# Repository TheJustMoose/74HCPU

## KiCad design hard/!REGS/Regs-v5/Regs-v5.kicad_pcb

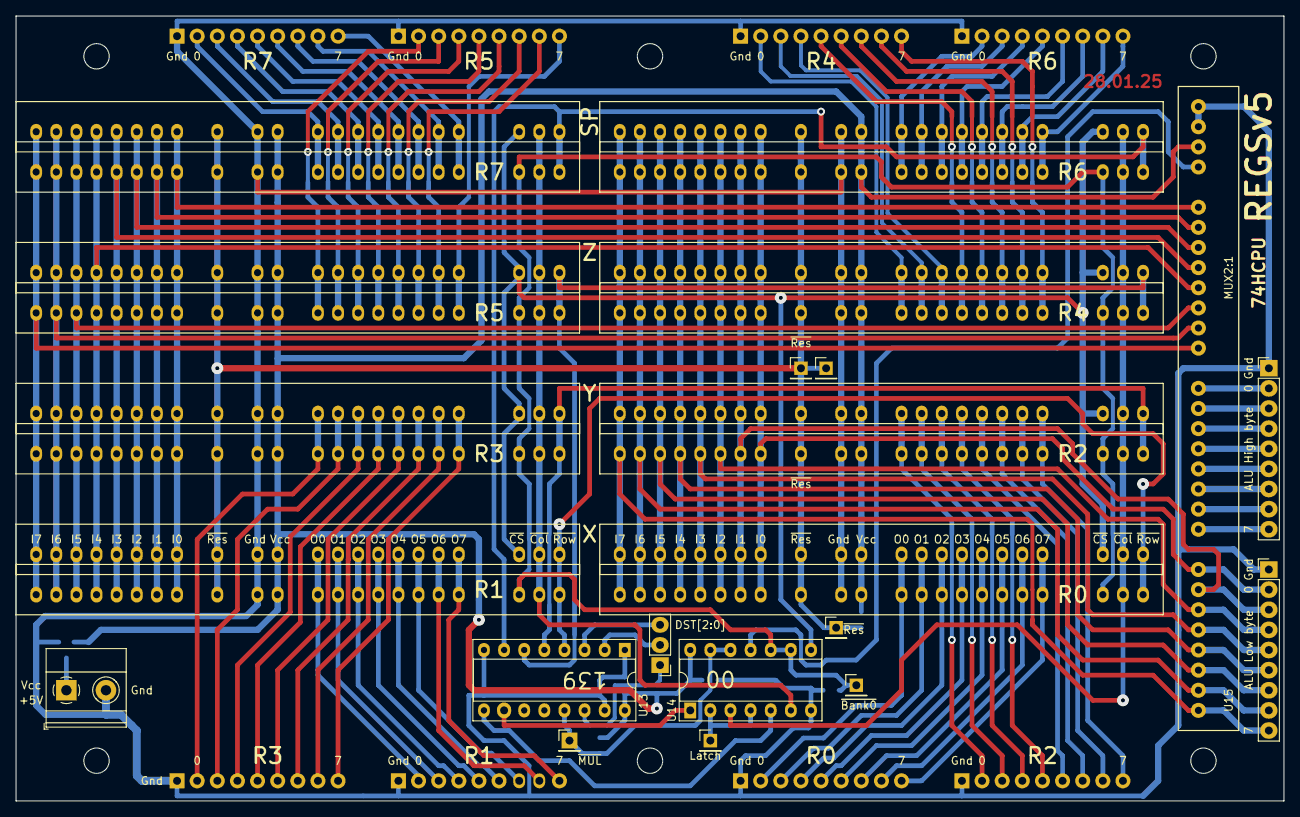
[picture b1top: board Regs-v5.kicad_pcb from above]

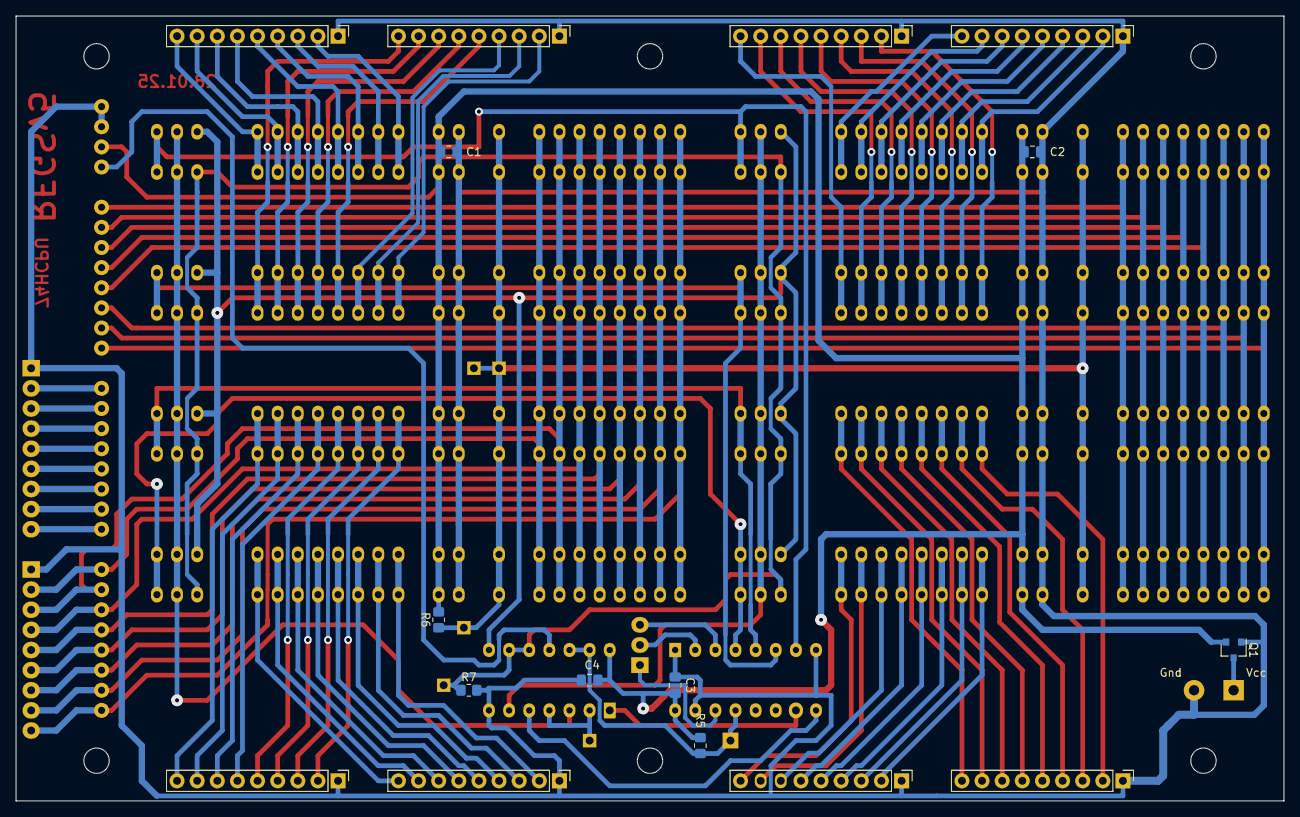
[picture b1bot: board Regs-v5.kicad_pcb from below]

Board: 2 copper layers, 160.0 x 99.1 mm, 51 parts (16 on the bottom side), 108 nets.

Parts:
C1, C2, C3, C4: 0.1uF; C_0805_2012Metric_Pad1.18x1.45mm_HandSolder
H1, H2, H3, H4, H5, H6: MountingHole; MountingHole_3.2mm_M3
J1, J2, J3, J4, J5, J6, J7, J8, J17, J18: Conn_01x09_Male; PinHeader_1x09_P2.54mm_Vertical
J11: Conn_01x03_Male; PinHeader_1x03_P2.54mm_Vertical
J12, J13, J14, J15, J19, J20: Conn_01x01_Male; PinHeader_1x01_P2.54mm_Vertical
J16: Screw_Terminal_01x02; TerminalBlock_Phoenix_MKDS-1,5-2_1x02_P5.00mm_Horizontal
Q1: IRLML5203; SOT-23
R5, R6, R7: 10k; R_0805_2012Metric_Pad1.20x1.40mm_HandSolder
U1, U2, U3, U4, U5, U6, U7, U8, U9, U10, U11, U12, U16, U17, U18, U19: REG_CNT
U13: 74LS139; DIP-16_W7.62mm_Socket
U14: 74HC00; DIP-14_W7.62mm_Socket
U15: MUX2-1; CMDwoC

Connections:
/ALU_H0: J18.2, U15.16
/ALU_H7: J18.9, U15.9
/DST[0]: J11.1, U13.14
/DST[1]: J11.2, U13.2
/DST[2]: J11.3, U13.3
/H0: U2.8, U4.8, U6.8, U8.8, U10.8, U12.8, U15.24, U17.8, U19.8
/H1: U2.7, U4.7, U6.7, U8.7, U10.7, U12.7, U15.23, U17.7, U19.7
/H2: U2.6, U4.6, U6.6, U8.6, U10.6, U12.6, U15.22, U17.6, U19.6
/H3: U2.5, U4.5, U6.5, U8.5, U10.5, U12.5, U15.21, U17.5, U19.5
/H4: U2.4, U4.4, U6.4, U8.4, U10.4, U12.4, U15.20, U17.4, U19.4
/H5: U2.3, U4.3, U6.3, U8.3, U10.3, U12.3, U15.19, U17.3, U19.3
/H6: U2.2, U4.2, U6.2, U8.2, U10.2, U12.2, U15.18, U17.2, U19.2
/H7: U2.1, U4.1, U6.1, U8.1, U10.1, U12.1, U15.17, U17.1, U19.1
/L0: J17.2, U1.8, U3.8, U5.8, U7.8, U9.8, U11.8, U15.8, U16.8, U18.8
/L1: J17.3, U1.7, U3.7, U5.7, U7.7, U9.7, U11.7, U15.7, U16.7, U18.7
/L2: J17.4, U1.6, U3.6, U5.6, U7.6, U9.6, U11.6, U15.6, U16.6, U18.6
/L3: J17.5, U1.5, U3.5, U5.5, U7.5, U9.5, U11.5, U15.5, U16.5, U18.5
/L4: J17.6, U1.4, U3.4, U5.4, U7.4, U9.4, U11.4, U15.4, U16.4, U18.4
/L5: J17.7, U1.3, U3.3, U5.3, U7.3, U9.3, U11.3, U15.3, U16.3, U18.3
/L6: J17.8, U1.2, U3.2, U5.2, U7.2, U9.2, U11.2, U15.2, U16.2, U18.2
/L7: J17.9, U1.1, U3.1, U5.1, U7.1, U9.1, U11.1, U15.1, U16.1, U18.1
/Latch: J15.1, U14.2, U14.4
/R0.0: J1.2, U1.12, U9.12
/R0.1: J1.3, U1.13, U9.13
/R0.2: J1.4, U1.14, U9.14
/R0.3: J1.5, U1.15, U9.15
/R0.4: J1.6, U1.16, U9.16
/R0.5: J1.7, U1.17, U9.17
/R0.6: J1.8, U1.18, U9.18
/R0.7: J1.9, U1.19, U9.19
/R1.0: J2.2, U2.12, U10.12
/R1.1: J2.3, U2.13, U10.13
/R1.2: J2.4, U2.14, U10.14
/R1.3: J2.5, U2.15, U10.15
/R1.4: J2.6, U2.16, U10.16
/R1.5: J2.7, U2.17, U10.17
/R1.6: J2.8, U2.18, U10.18
/R1.7: J2.9, U2.19, U10.19
/R2.0: J3.2, U3.12, U11.12
/R2.1: J3.3, U3.13, U11.13
/R2.2: J3.4, U3.14, U11.14
/R2.3: J3.5, U3.15, U11.15
/R2.4: J3.6, U3.16, U11.16
/R2.5: J3.7, U3.17, U11.17
/R2.6: J3.8, U3.18, U11.18
/R2.7: J3.9, U3.19, U11.19
/R3.0: J4.2, U4.12, U12.12
/R3.1: J4.3, U4.13, U12.13
/R3.2: J4.4, U4.14, U12.14
/R3.3: J4.5, U4.15, U12.15
/R3.4: J4.6, U4.16, U12.16
/R3.5: J4.7, U4.17, U12.17
/R3.6: J4.8, U4.18, U12.18
/R3.7: J4.9, U4.19, U12.19
/R4.0: J5.2, U5.12, U16.12
/R4.1: J5.3, U5.13, U16.13
/R4.2: J5.4, U5.14, U16.14
/R4.3: J5.5, U5.15, U16.15
/R4.4: J5.6, U5.16, U16.16
/R4.5: J5.7, U5.17, U16.17
/R4.6: J5.8, U5.18, U16.18
/R4.7: J5.9, U5.19, U16.19
/R5.0: J6.2, U6.12, U17.12
/R5.1: J6.3, U6.13, U17.13
/R5.2: J6.4, U6.14, U17.14
/R5.3: J6.5, U6.15, U17.15
/R5.4: J6.6, U6.16, U17.16
/R5.5: J6.7, U6.17, U17.17
/R5.6: J6.8, U6.18, U17.18
/R5.7: J6.9, U6.19, U17.19
/R6.0: J7.2, U7.12, U18.12
/R6.1: J7.3, U7.13, U18.13
/R6.2: J7.4, U7.14, U18.14
/R6.3: J7.5, U7.15, U18.15
/R6.4: J7.6, U7.16, U18.16
/R6.5: J7.7, U7.17, U18.17
/R6.6: J7.8, U7.18, U18.18
/R6.7: J7.9, U7.19, U18.19
/R7.0: J8.2, U8.12, U19.12
/R7.1: J8.3, U8.13, U19.13
/R7.2: J8.4, U8.14, U19.14
/R7.3: J8.5, U8.15, U19.15
/R7.4: J8.6, U8.16, U19.16
/R7.5: J8.7, U8.17, U19.17
/R7.6: J8.8, U8.18, U19.18
/R7.7: J8.9, U8.19, U19.19
/~Bank0: J14.1, R7.1, U1.20, U2.20, U3.20, U4.20, U5.20, U6.20, U7.20, U8.20, U14.9, U14.10
/~Bank1: U9.20, U10.20, U11.20, U12.20, U14.8, U16.20, U17.20, U18.20, U19.20
/~H: U2.21, U4.21, U6.21, U8.21, U10.21, U12.21, U14.6, U17.21, U19.21
/~L: U1.21, U3.21, U5.21, U7.21, U9.21, U11.21, U14.3, U16.21, U18.21
/~MUL: J12.1, R5.1, U13.13, U14.12, U14.13
/~R0: U1.22, U2.22, U9.22, U10.22, U13.4
/~R1: U3.22, U4.22, U11.22, U12.22, U13.5
/~R2: U5.22, U6.22, U13.6, U16.22, U17.22
/~R3: U7.22, U8.22, U13.7, U18.22, U19.22
/~Res: J13.1, J19.1, J20.1, R6.1, U1.9, U2.9, U3.9, U4.9, U5.9, U6.9, U7.9, U8.9, U9.9, U10.9, U11.9, U12.9, U16.9, U17.9, U18.9, U19.9
GND: C1.2, C2.2, C3.2, C4.2, J1.1, J2.1, J3.1, J4.1, J5.1, J6.1, J7.1, J8.1, J16.2, J17.1, J18.1, Q1.1, R7.2, U1.10, U2.10, U3.10, U4.10, U5.10, U6.10, U7.10, U8.10, U9.10, U10.10, U11.10, U12.10, U13.1, U13.8, U13.15, U14.7, U15.27, U15.28, U16.10, U17.10, U18.10, U19.10
unnamed: J16.1, Q1.3
unnamed: J18.3, U15.15
unnamed: J18.4, U15.14
unnamed: J18.5, U15.13
unnamed: J18.6, U15.12
unnamed: J18.7, U15.11
unnamed: J18.8, U15.10
unnamed: U13.9, U14.5
unnamed: U13.10, U14.1
unnamed: U14.11, U15.25
VCC: C1.1, C2.1, C3.1, C4.1, Q1.2, R5.2, R6.2, U1.11, U2.11, U3.11, U4.11, U5.11, U6.11, U7.11, U8.11, U9.11, U10.11, U11.11, U12.11, U13.16, U14.14, U15.26, U16.11, U17.11, U18.11, U19.11

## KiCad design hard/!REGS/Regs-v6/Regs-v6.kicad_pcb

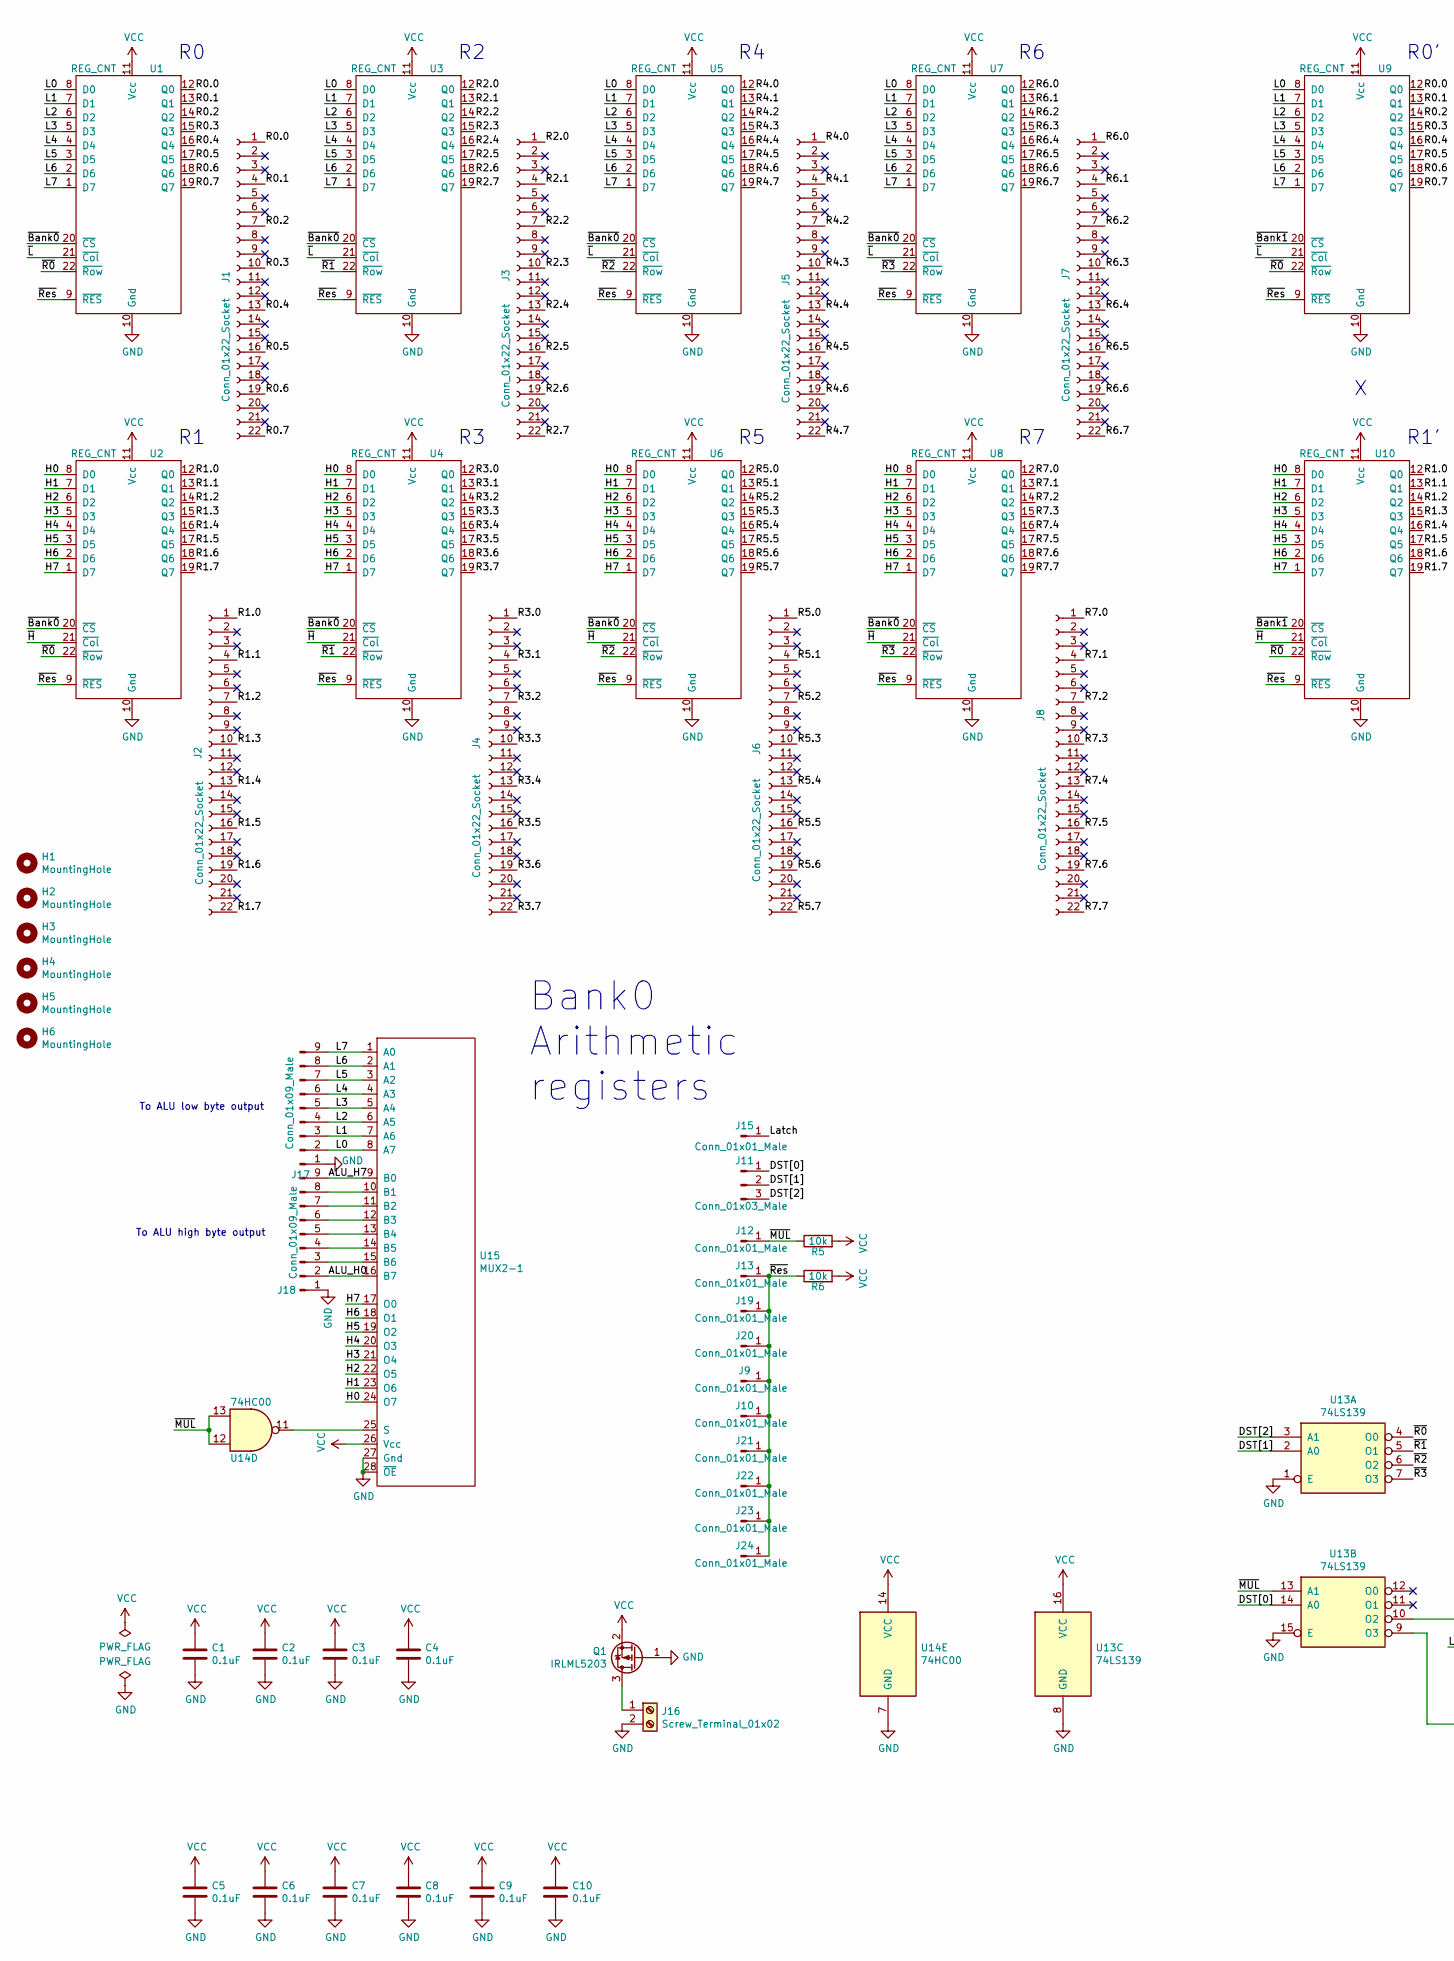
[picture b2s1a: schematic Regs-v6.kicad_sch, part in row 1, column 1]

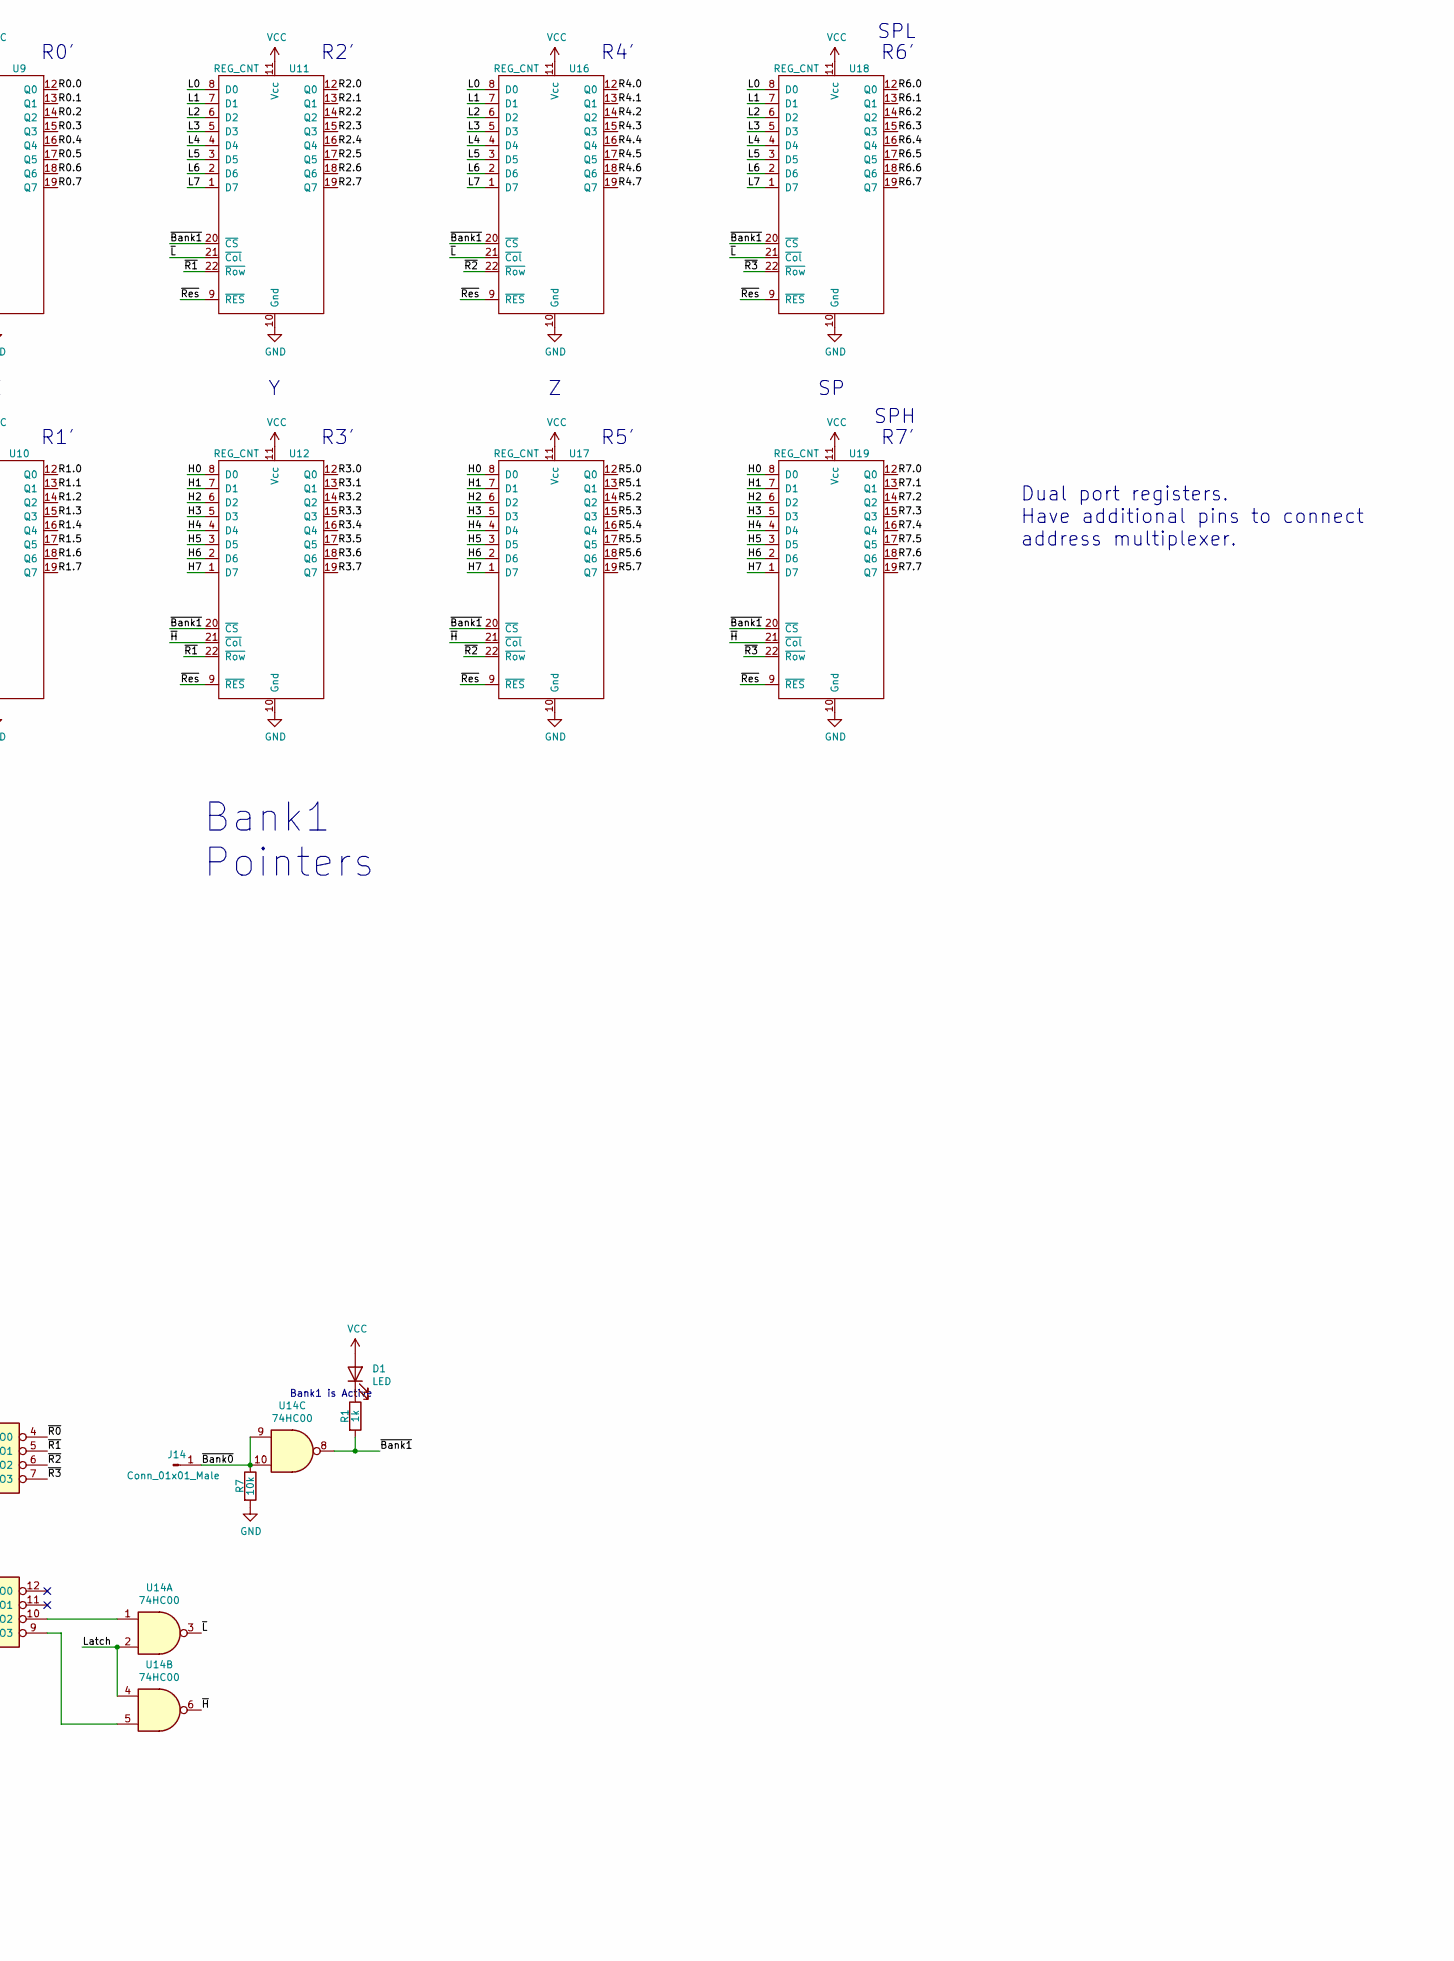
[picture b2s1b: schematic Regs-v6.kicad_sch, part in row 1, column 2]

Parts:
C1, C2, C3, C4, C5, C6, C7, C8, C9, C10: 0.1uF; C_0805_2012Metric_Pad1.18x1.45mm_HandSolder
D1: LED; LED_D5.0mm
H1, H2, H3, H4, H5, H6: MountingHole; MountingHole_3.2mm_M3
J1, J2, J3, J4, J5, J6, J7, J8: Conn_01x22_Socket; PinSocket_1x22_P2.54mm_Vertical
J9, J10, J12, J13, J14, J15, J19, J20, J21, J22, J23, J24: Conn_01x01_Male; PinHeader_1x01_P2.54mm_Vertical
J11: Conn_01x03_Male; PinHeader_1x03_P2.54mm_Vertical
J16: Screw_Terminal_01x02; TerminalBlock_Phoenix_MKDS-1,5-2_1x02_P5.00mm_Horizontal
J17, J18: Conn_01x09_Male; PinHeader_1x09_P2.54mm_Vertical
Q1: IRLML5203; SOT-23
R1: 1k; R_0805_2012Metric_Pad1.20x1.40mm_HandSolder
R5, R6, R7: 10k; R_0805_2012Metric_Pad1.20x1.40mm_HandSolder
U1, U2, U3, U4, U5, U6, U7, U8, U9, U10, U11, U12, U16, U17, U18, U19: REG_CNT
U13: 74LS139; DIP-16_W7.62mm_Socket
U14: 74HC00; DIP-14_W7.62mm_Socket
U15: MUX2-1; CMDwoC

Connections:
/ALU_H0: J18.2, U15.16 (B7)
/ALU_H7: J18.9, U15.9 (B0)
/DST[0]: J11.1, U13.14 (A0)
/DST[1]: J11.2, U13.2 (A0)
/DST[2]: J11.3, U13.3 (A1)
/H0: U2.8 (D0), U4.8 (D0), U6.8 (D0), U8.8 (D0), U10.8 (D0), U12.8 (D0), U15.24 (O7), U17.8 (D0), U19.8 (D0)
/H1: U2.7 (D1), U4.7 (D1), U6.7 (D1), U8.7 (D1), U10.7 (D1), U12.7 (D1), U15.23 (O6), U17.7 (D1), U19.7 (D1)
/H2: U2.6 (D2), U4.6 (D2), U6.6 (D2), U8.6 (D2), U10.6 (D2), U12.6 (D2), U15.22 (O5), U17.6 (D2), U19.6 (D2)
/H3: U2.5 (D3), U4.5 (D3), U6.5 (D3), U8.5 (D3), U10.5 (D3), U12.5 (D3), U15.21 (O4), U17.5 (D3), U19.5 (D3)
/H4: U2.4 (D4), U4.4 (D4), U6.4 (D4), U8.4 (D4), U10.4 (D4), U12.4 (D4), U15.20 (O3), U17.4 (D4), U19.4 (D4)
/H5: U2.3 (D5), U4.3 (D5), U6.3 (D5), U8.3 (D5), U10.3 (D5), U12.3 (D5), U15.19 (O2), U17.3 (D5), U19.3 (D5)
/H6: U2.2 (D6), U4.2 (D6), U6.2 (D6), U8.2 (D6), U10.2 (D6), U12.2 (D6), U15.18 (O1), U17.2 (D6), U19.2 (D6)
/H7: U2.1 (D7), U4.1 (D7), U6.1 (D7), U8.1 (D7), U10.1 (D7), U12.1 (D7), U15.17 (O0), U17.1 (D7), U19.1 (D7)
/L0: J17.2, U1.8 (D0), U3.8 (D0), U5.8 (D0), U7.8 (D0), U9.8 (D0), U11.8 (D0), U15.8 (A7), U16.8 (D0), U18.8 (D0)
/L1: J17.3, U1.7 (D1), U3.7 (D1), U5.7 (D1), U7.7 (D1), U9.7 (D1), U11.7 (D1), U15.7 (A6), U16.7 (D1), U18.7 (D1)
/L2: J17.4, U1.6 (D2), U3.6 (D2), U5.6 (D2), U7.6 (D2), U9.6 (D2), U11.6 (D2), U15.6 (A5), U16.6 (D2), U18.6 (D2)
/L3: J17.5, U1.5 (D3), U3.5 (D3), U5.5 (D3), U7.5 (D3), U9.5 (D3), U11.5 (D3), U15.5 (A4), U16.5 (D3), U18.5 (D3)
/L4: J17.6, U1.4 (D4), U3.4 (D4), U5.4 (D4), U7.4 (D4), U9.4 (D4), U11.4 (D4), U15.4 (A3), U16.4 (D4), U18.4 (D4)
/L5: J17.7, U1.3 (D5), U3.3 (D5), U5.3 (D5), U7.3 (D5), U9.3 (D5), U11.3 (D5), U15.3 (A2), U16.3 (D5), U18.3 (D5)
/L6: J17.8, U1.2 (D6), U3.2 (D6), U5.2 (D6), U7.2 (D6), U9.2 (D6), U11.2 (D6), U15.2 (A1), U16.2 (D6), U18.2 (D6)
/L7: J17.9, U1.1 (D7), U3.1 (D7), U5.1 (D7), U7.1 (D7), U9.1 (D7), U11.1 (D7), U15.1 (A0), U16.1 (D7), U18.1 (D7)
/Latch: J15.1, U14.2, U14.4
/R0.0: J1.1, U1.12 (Q0), U9.12 (Q0)
/R0.1: J1.4, U1.13 (Q1), U9.13 (Q1)
/R0.2: J1.7, U1.14 (Q2), U9.14 (Q2)
/R0.3: J1.10, U1.15 (Q3), U9.15 (Q3)
/R0.4: J1.13, U1.16 (Q4), U9.16 (Q4)
/R0.5: J1.16, U1.17 (Q5), U9.17 (Q5)
/R0.6: J1.19, U1.18 (Q6), U9.18 (Q6)
/R0.7: J1.22, U1.19 (Q7), U9.19 (Q7)
/R1.0: J2.1, U2.12 (Q0), U10.12 (Q0)
/R1.1: J2.4, U2.13 (Q1), U10.13 (Q1)
/R1.2: J2.7, U2.14 (Q2), U10.14 (Q2)
/R1.3: J2.10, U2.15 (Q3), U10.15 (Q3)
/R1.4: J2.13, U2.16 (Q4), U10.16 (Q4)
/R1.5: J2.16, U2.17 (Q5), U10.17 (Q5)
/R1.6: J2.19, U2.18 (Q6), U10.18 (Q6)
/R1.7: J2.22, U2.19 (Q7), U10.19 (Q7)
/R2.0: J3.1, U3.12 (Q0), U11.12 (Q0)
/R2.1: J3.4, U3.13 (Q1), U11.13 (Q1)
/R2.2: J3.7, U3.14 (Q2), U11.14 (Q2)
/R2.3: J3.10, U3.15 (Q3), U11.15 (Q3)
/R2.4: J3.13, U3.16 (Q4), U11.16 (Q4)
/R2.5: J3.16, U3.17 (Q5), U11.17 (Q5)
/R2.6: J3.19, U3.18 (Q6), U11.18 (Q6)
/R2.7: J3.22, U3.19 (Q7), U11.19 (Q7)
/R3.0: J4.1, U4.12 (Q0), U12.12 (Q0)
/R3.1: J4.4, U4.13 (Q1), U12.13 (Q1)
/R3.2: J4.7, U4.14 (Q2), U12.14 (Q2)
/R3.3: J4.10, U4.15 (Q3), U12.15 (Q3)
/R3.4: J4.13, U4.16 (Q4), U12.16 (Q4)
/R3.5: J4.16, U4.17 (Q5), U12.17 (Q5)
/R3.6: J4.19, U4.18 (Q6), U12.18 (Q6)
/R3.7: J4.22, U4.19 (Q7), U12.19 (Q7)
/R4.0: J5.1, U5.12 (Q0), U16.12 (Q0)
/R4.1: J5.4, U5.13 (Q1), U16.13 (Q1)
/R4.2: J5.7, U5.14 (Q2), U16.14 (Q2)
/R4.3: J5.10, U5.15 (Q3), U16.15 (Q3)
/R4.4: J5.13, U5.16 (Q4), U16.16 (Q4)
/R4.5: J5.16, U5.17 (Q5), U16.17 (Q5)
/R4.6: J5.19, U5.18 (Q6), U16.18 (Q6)
/R4.7: J5.22, U5.19 (Q7), U16.19 (Q7)
/R5.0: J6.1, U6.12 (Q0), U17.12 (Q0)
/R5.1: J6.4, U6.13 (Q1), U17.13 (Q1)
/R5.2: J6.7, U6.14 (Q2), U17.14 (Q2)
/R5.3: J6.10, U6.15 (Q3), U17.15 (Q3)
/R5.4: J6.13, U6.16 (Q4), U17.16 (Q4)
/R5.5: J6.16, U6.17 (Q5), U17.17 (Q5)
/R5.6: J6.19, U6.18 (Q6), U17.18 (Q6)
/R5.7: J6.22, U6.19 (Q7), U17.19 (Q7)
/R6.0: J7.1, U7.12 (Q0), U18.12 (Q0)
/R6.1: J7.4, U7.13 (Q1), U18.13 (Q1)
/R6.2: J7.7, U7.14 (Q2), U18.14 (Q2)
/R6.3: J7.10, U7.15 (Q3), U18.15 (Q3)
/R6.4: J7.13, U7.16 (Q4), U18.16 (Q4)
/R6.5: J7.16, U7.17 (Q5), U18.17 (Q5)
/R6.6: J7.19, U7.18 (Q6), U18.18 (Q6)
/R6.7: J7.22, U7.19 (Q7), U18.19 (Q7)
/R7.0: J8.1, U8.12 (Q0), U19.12 (Q0)
/R7.1: J8.4, U8.13 (Q1), U19.13 (Q1)
/R7.2: J8.7, U8.14 (Q2), U19.14 (Q2)
/R7.3: J8.10, U8.15 (Q3), U19.15 (Q3)
/R7.4: J8.13, U8.16 (Q4), U19.16 (Q4)
/R7.5: J8.16, U8.17 (Q5), U19.17 (Q5)
/R7.6: J8.19, U8.18 (Q6), U19.18 (Q6)
/R7.7: J8.22, U8.19 (Q7), U19.19 (Q7)
/~Bank0: J14.1, R7.1, U1.20 (~CS), U2.20 (~CS), U3.20 (~CS), U4.20 (~CS), U5.20 (~CS), U6.20 (~CS), U7.20 (~CS), U8.20 (~CS), U14.9, U14.10
/~Bank1: R1.2, U9.20 (~CS), U10.20 (~CS), U11.20 (~CS), U12.20 (~CS), U14.8, U16.20 (~CS), U17.20 (~CS), U18.20 (~CS), U19.20 (~CS)
/~H: U2.21 (~Col), U4.21 (~Col), U6.21 (~Col), U8.21 (~Col), U10.21 (~Col), U12.21 (~Col), U14.6, U17.21 (~Col), U19.21 (~Col)
/~L: U1.21 (~Col), U3.21 (~Col), U5.21 (~Col), U7.21 (~Col), U9.21 (~Col), U11.21 (~Col), U14.3, U16.21 (~Col), U18.21 (~Col)
/~MUL: J12.1, R5.1, U13.13 (A1), U14.12, U14.13
/~R0: U1.22 (~Row), U2.22 (~Row), U9.22 (~Row), U10.22 (~Row), U13.4 (O0)
/~R1: U3.22 (~Row), U4.22 (~Row), U11.22 (~Row), U12.22 (~Row), U13.5 (O1)
/~R2: U5.22 (~Row), U6.22 (~Row), U13.6 (O2), U16.22 (~Row), U17.22 (~Row)
/~R3: U7.22 (~Row), U8.22 (~Row), U13.7 (O3), U18.22 (~Row), U19.22 (~Row)
/~Res: J9.1, J10.1, J13.1, J19.1, J20.1, J21.1, J22.1, J23.1, J24.1, R6.1, U1.9 (~RES), U2.9 (~RES), U3.9 (~RES), U4.9 (~RES), U5.9 (~RES), U6.9 (~RES), U7.9 (~RES), U8.9 (~RES), U9.9 (~RES), U10.9 (~RES), U11.9 (~RES), U12.9 (~RES), U16.9 (~RES), U17.9 (~RES), U18.9 (~RES), U19.9 (~RES)
GND: C1.2, C2.2, C3.2, C4.2, C5.2, C6.2, C7.2, C8.2, C9.2, C10.2, J16.2, J17.1, J18.1, Q1.1 (G), R7.2, U1.10 (Gnd), U2.10 (Gnd), U3.10 (Gnd), U4.10 (Gnd), U5.10 (Gnd), U6.10 (Gnd), U7.10 (Gnd), U8.10 (Gnd), U9.10 (Gnd), U10.10 (Gnd), U11.10 (Gnd), U12.10 (Gnd), U13.1 (E), U13.8 (GND), U13.15 (E), U14.7 (GND), U15.27 (Gnd), U15.28 (~OE), U16.10 (Gnd), U17.10 (Gnd), U18.10 (Gnd), U19.10 (Gnd)
unnamed: D1.1 (K), R1.1
unnamed: J16.1, Q1.3 (D)
unnamed: J18.3, U15.15 (B6)
unnamed: J18.4, U15.14 (B5)
unnamed: J18.5, U15.13 (B4)
unnamed: J18.6, U15.12 (B3)
unnamed: J18.7, U15.11 (B2)
unnamed: J18.8, U15.10 (B1)
unnamed: U13.10 (O2), U14.1
unnamed: U13.9 (O3), U14.5
unnamed: U14.11, U15.25 (S)
VCC: C1.1, C2.1, C3.1, C4.1, C5.1, C6.1, C7.1, C8.1, C9.1, C10.1, D1.2 (A), Q1.2 (S), R5.2, R6.2, U1.11 (Vcc), U2.11 (Vcc), U3.11 (Vcc), U4.11 (Vcc), U5.11 (Vcc), U6.11 (Vcc), U7.11 (Vcc), U8.11 (Vcc), U9.11 (Vcc), U10.11 (Vcc), U11.11 (Vcc), U12.11 (Vcc), U13.16 (VCC), U14.14 (VCC), U15.26 (Vcc), U16.11 (Vcc), U17.11 (Vcc), U18.11 (Vcc), U19.11 (Vcc)

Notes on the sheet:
SPH
To ALU high byte output
To ALU low byte output
R5'
R4'
Bank1 is Active
Dual port registers. Have additional pins to connect address multiplexer.
R2'
R1'
Bank1 Pointers
R7'
Bank0 Arithmetic registers
SPL
R3'
R0'
R6'

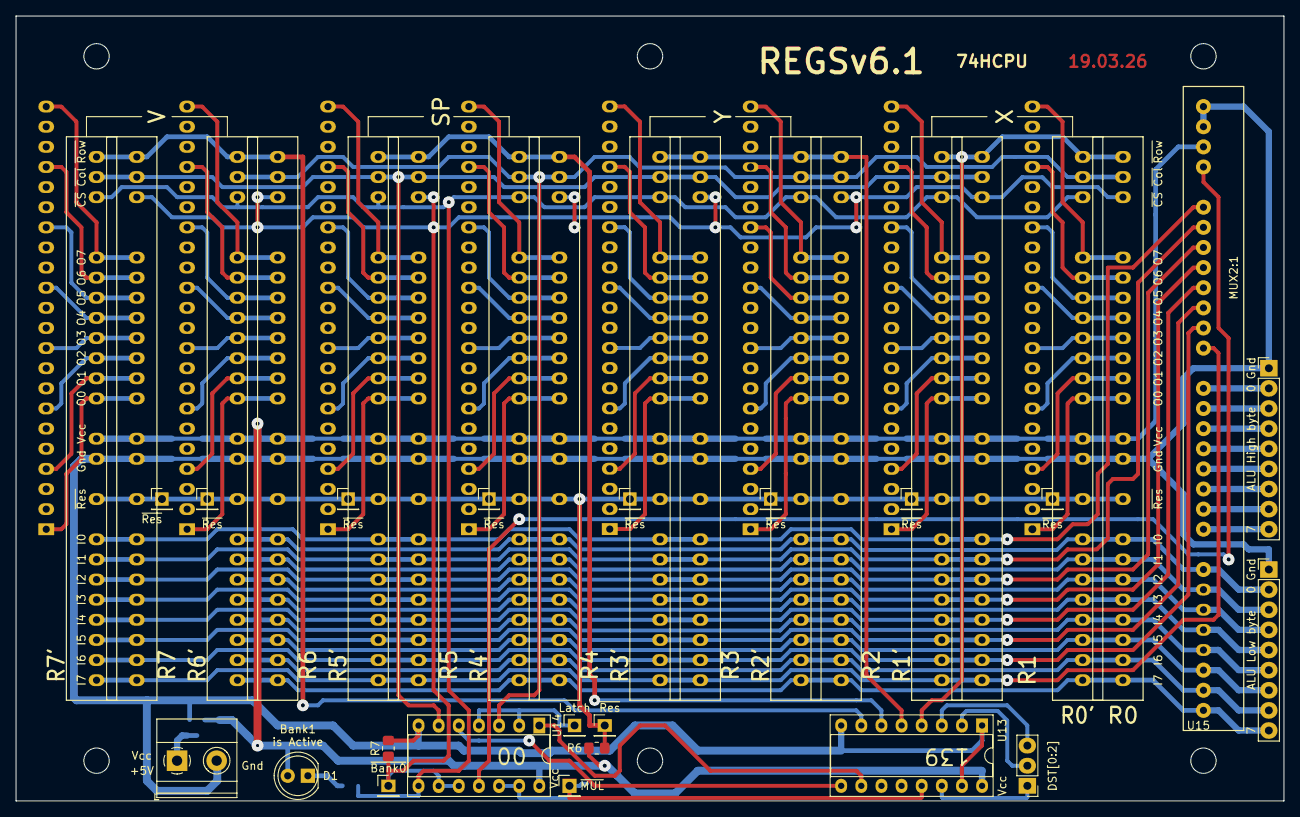
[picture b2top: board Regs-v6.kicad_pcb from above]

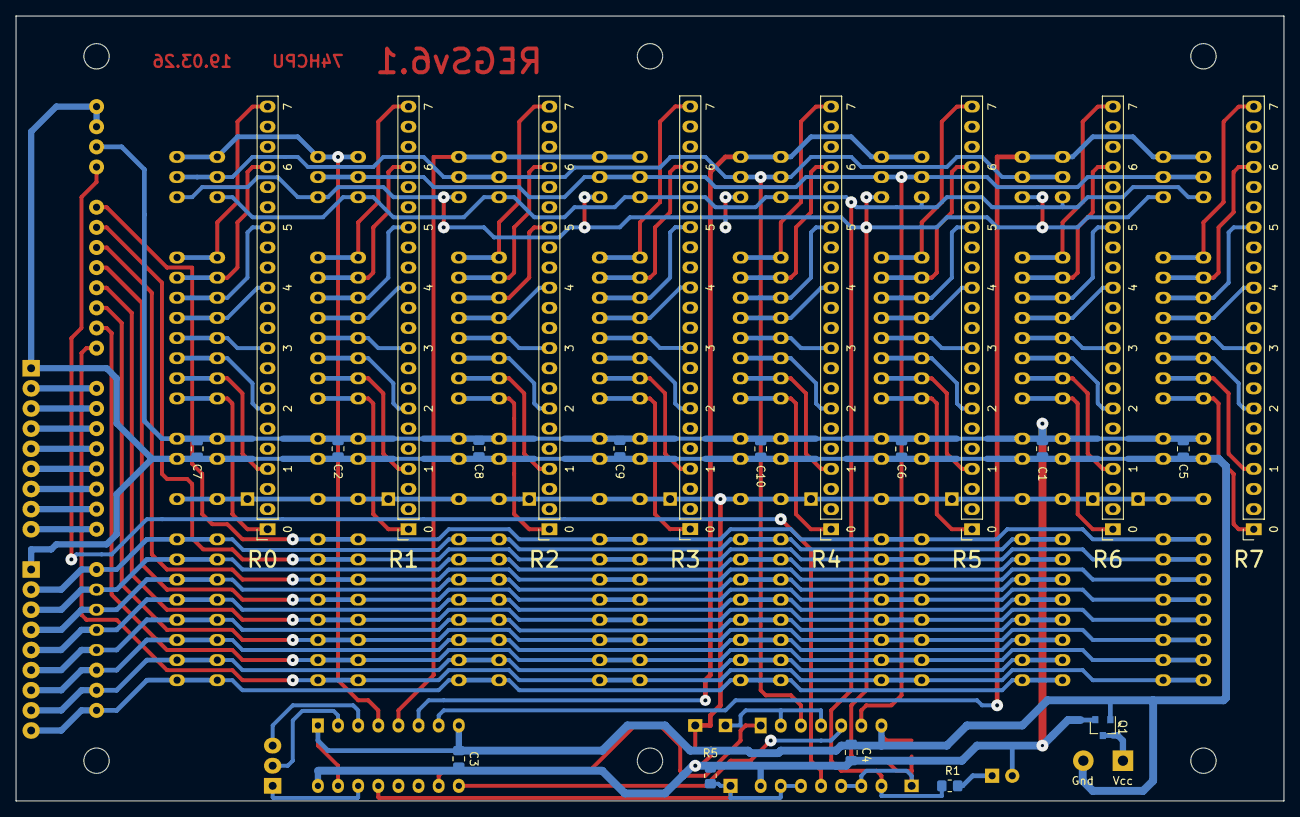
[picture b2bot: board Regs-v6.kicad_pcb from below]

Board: 2 copper layers, 160.0 x 99.1 mm, 65 parts (21 on the bottom side), 109 nets.
